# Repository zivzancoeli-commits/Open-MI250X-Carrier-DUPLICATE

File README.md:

> **DUPLICATE working copy — not the original.**
> Original: https://github.com/zivzancoeli-commits/Open-MI250X-Carrier
> Marked duplicate: 2026-08-21

# Open MI250X Carrier

## Purpose
This project collects public evidence needed to design a minimal open-source carrier board for surplus AMD Instinct MI250X OAM modules. It is organized as a reverse-engineering knowledge base: public documentation is collected first, facts are extracted into notes, and unknown or proprietary behavior is tracked instead of assumed.

## Workflow
- Collect public links and local reference copies in [02_AMD_Docs](02_AMD_Docs/) and [13_Reference_Docs](13_Reference_Docs/).
- Extract design-relevant facts into [09_AI_Notes](09_AI_Notes/), separating verified information from questions.
- Use research in [08_Research_Papers](08_Research_Papers/) to understand topology, bandwidth, and system context before design decisions.
- Carry verified mechanical, PCIe, power, cooling, firmware, and software assumptions into schematic, layout, prototype, and validation work.

## Top-Level Folders
- [02_AMD_Docs](02_AMD_Docs/): upstream public links for OAM, AMD matrix cores, ROCm compatibility, and MI250X software support.
- [08_Research_Papers](08_Research_Papers/): architecture and data-movement research, currently focused on topology and bandwidth.
- [09_AI_Notes](09_AI_Notes/): topic notes for architecture, PCIe, power, cooling, clocking, management, ideas, questions, and unknowns.
- [13_Reference_Docs](13_Reference_Docs/): local indexes and reference material for AMD, ROCm, OAM/OCP, Molex, cooling, firmware, memory, and components.

## Known Information
- Manual project status items: gather public documentation, understand OAM, identify undocumented interfaces, create architecture, draw schematic, PCB layout, prototype.
- Manual note: undocumented behavior should be tracked as an open question rather than assumed.
- `Wanted_Documents.rtf` tracks OAM, AMD, PCIe, power, cooling, and photo references; no image files are currently present.
- MP2975 is listed as believed present on MI250X, but not visually confirmed.

## Project Roadmap
1. Documentation Collection
2. Knowledge Extraction
3. Reverse Engineering
4. Schematic Design
5. PCB Layout
6. Prototype
7. Bring-up and Validation

## Open Questions
- Mechanical, baseboard, connector, PCIe routing, REFCLK, PMBus, VRM, and OAM thermal references are listed as missing or incomplete.
- Three local PDFs could not be read because they report invalid PDF structure.

## TODO
- Keep `Wanted_Documents.rtf` aligned with files added under `13_Reference_Docs`.
- Move verified findings into `09_AI_Notes` with clear evidence and uncertainty labels.

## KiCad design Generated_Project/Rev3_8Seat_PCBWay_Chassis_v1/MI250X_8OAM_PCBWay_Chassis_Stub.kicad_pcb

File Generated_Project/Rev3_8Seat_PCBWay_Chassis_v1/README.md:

# Rev3 — 8-seat chassis, 2-module first article (POWER+MECH)

**DO NOT ENERGIZE P48V** until Molex 1.2 A/contact at 48–59.5 V (2 oz) is written (ticket 167157).  
**Do not upload from this agent.** Eli uploads `fab/Rev3_8Seat_PCBWay_12L_492x372_qty5_gerbers.zip` if he accepts it.

Chamber B **OAM chassis PCB** only. Not a motherboard. Do not swap X11DPH-T.

- **First-article target: seats 0–1.** Without overlay, 2× MI250X = two modules **sit** and at most **GCD0** on each can be targeted (**2 GCDs**). **Not** 2× full-width (**4 GCDs**).
- Legal host PE today: Conn0 OCP `PCIE_*` = `PE_S0_GCD0_x16` + `PE_S1_GCD0_x16` toward the host keepout. GCD1 named-only. Not S1–S7. Conn1 has **0** `PCIE_*`.
- Host X11DPH-T: two GCD0 x16 **fit**; two full-width modules **do not**. **No CEM/MCIO MPN invented.**
- Same PCB populate **2 → 4 → 8**. Later-seat x16 names + SW0–SW3 DNP kept. Do not stuff switches this article.
- Pin names: OCP generic **v1.0**. **v1.x only.** r2.0 is UNUSABLE. P3V3 = Conn0 C1/C2.
- **P48V:** Anderson **6325G1** + 2× **1382** → star spines (not a 100 A flood) → per-seat **0476015.MR** 15 A. First populate F0/F1. Off-board 48 V: 240 V / 50 A single-phase class — **not** RST-5000-48 (3-phase).
- **P12V1 / P3V3:** **THL 40-4812WI** (40 W from 48 V) + **OKI-78SR-3.3/1.5-W36-C** (4.95 W from P12V1). No GPU VRM.
- TEST*/RFU/DO_NOT_USE **unmapped**. PVREF **not driven**. S1–S7 **no net**.
- Silk keeps **DO NOT ENERGIZE P48V**. PE stays unrouted (DNP switches).

| File | What |
|---|---|
| `fab/Rev3_8Seat_PCBWay_12L_492x372_qty5_gerbers.zip` | Gerbers, drill, IPC-356, PnP, FAB_NOTES, BOM |
| `docs/STATUS.md` | What Eli can upload vs what stays DNP |
| `docs/EPYC_2P_PUBLIC_SKETCH.md` | Public-facts 2P EPYC host sketch. **DO NOT FAB.** No SP5 pins, xGMI routes, SVI3 phases, or Gerbers. Buy H13/H14, MZ73, TURIN2D/GENOA2D, or AS-4124GQ-TNMI. Dual SP5 has 4× MI250X lanes; overlay still missing. |
| `docs/CONCEPT_8x_FULL_WIDTH.md` | Pointer to 8× full-width **CONCEPT** (ideas only) |
| `docs/LATE_BIND.md` | Pointer: reserved vs later-spin (**respin**, not silk ECO) |
| [`../Rev3_8Seat_FULLWIDTH_CONCEPT/LATE_BIND.md`](../Rev3_8Seat_FULLWIDTH_CONCEPT/LATE_BIND.md) | Late-bind table. **DO NOT FABRICATE** live PE. |
| [`../Rev3_8Seat_FULLWIDTH_CONCEPT/CONCEPT.md`](../Rev3_8Seat_FULLWIDTH_CONCEPT/CONCEPT.md) | 8× full-width fabric sketch. **DO NOT FABRICATE.** X11DPH-T cannot light 256 DS. |
| `docs/FAB_NOTES.md` | Stackup, skip-pin NC, do-not-energize |
| `docs/PCBWAY.md` | Guest quotes 2026-08-21. Agent does not upload. |
| `BOM.md` | PCB bill with buyable MPNs |
| `docs/previews/` | Top SVG/PNG |

```
python3 Generated_Project/Rev3_8Seat_PCBWay_Chassis_v1/tools/generate_from_v10_pinmap.py
python3 Generated_Project/Rev3_8Seat_PCBWay_Chassis_v1/tools/export_fab.py
```

Do not “Update PCB from Schematic”. Do not stuff PM8536 on this article. Do not upload to PCBWay from this tree. First article still cannot run 2 live GPUs without maps. **This zip will not work as a live GPU chassis if sent to PCBWay.**

**8× full-width CONCEPT** (sibling folder): ideas only. **DO NOT FABRICATE** as live PE. **DO NOT ENERGIZE.** Host stays X11DPH-T and **cannot light 8× full-width**. Routing 16× x16 + four 1311-ball escapes is a **respin** (`LATE_BIND.md`).

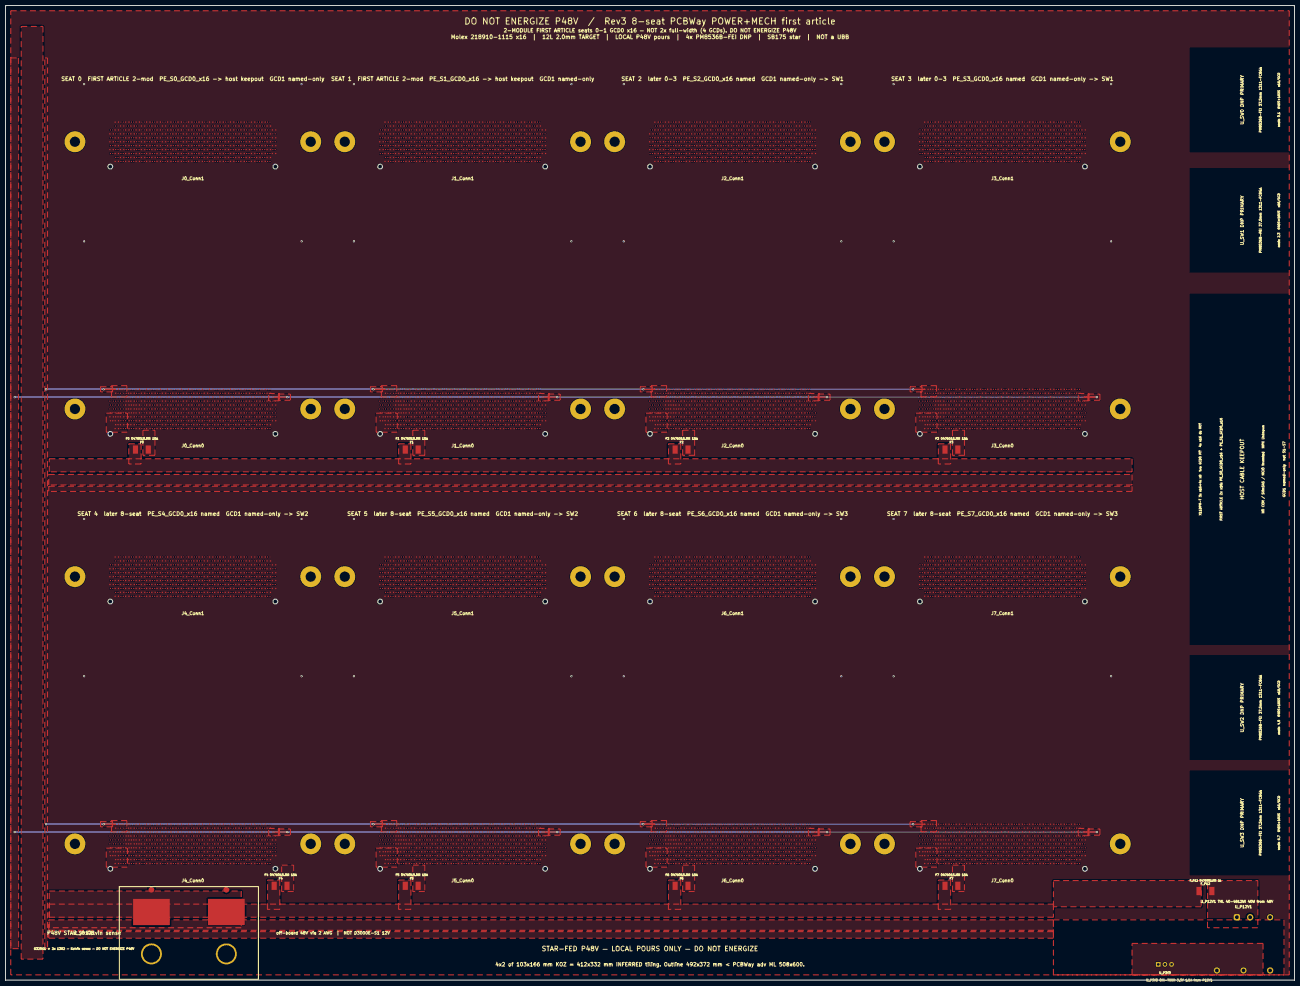
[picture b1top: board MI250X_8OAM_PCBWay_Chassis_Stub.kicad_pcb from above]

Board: 12 copper layers, 492.0 x 372.0 mm, 60 parts (0 on the bottom side), 22 nets.

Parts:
F0, F1, F2, F3, F4, F5, F6, F7: 0476015.MR; Fuse_Littelfuse-NANO2-451_453
F_P12: 0476002.MR; Fuse_Littelfuse-NANO2-451_453
H01, H02, H03, H04, H11, H12, H13, H14, H21, H22, H23, H24, H31, H32, H33, H34, H41, H42, H43, H44, H51, H52, H53, H54, H61, H62, H63, H64, H71, H72, H73, H74: NPTH_3.9; NPTH_3.9_Fig2
J0_Conn0, J0_Conn1, J1_Conn0, J1_Conn1, J2_Conn0, J2_Conn1, J3_Conn0, J3_Conn1, J4_Conn0, J4_Conn1, J5_Conn0, J5_Conn1, J6_Conn0, J6_Conn1, J7_Conn0, J7_Conn1: 218910-1115; 218910-1115_candidate
J_SB175: 6325G1_SB175; Anderson_SB175_2pole
U_P3V3: OKI-78SR-3.3/1.5-W36-C; Converter_DCDC_Murata_OKI-78SR_Vertical
U_P12V1: THL 40-4812WI; Converter_DCDC_TRACO_THL40-xxxxWI_THT

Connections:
GND: J0_Conn0.A5, J0_Conn0.A6, J0_Conn0.A9, J0_Conn0.A10, J0_Conn0.A13, J0_Conn0.A14, J0_Conn0.A17, J0_Conn0.A18, J0_Conn0.A21, J0_Conn0.A22, J0_Conn0.A25, J0_Conn0.A26, J0_Conn0.A29, J0_Conn0.A30, J0_Conn0.A33, J0_Conn0.A34, J0_Conn0.A37, J0_Conn0.A38, J0_Conn0.A41, J0_Conn0.A42, J0_Conn0.A45, J0_Conn0.A46, J0_Conn0.A49, J0_Conn0.A50, J0_Conn0.A53, J0_Conn0.A54, J0_Conn0.A57, J0_Conn0.A58, J0_Conn0.B3, J0_Conn0.B4, J0_Conn0.B7, J0_Conn0.B8, J0_Conn0.B11, J0_Conn0.B12, J0_Conn0.B15, J0_Conn0.B16, J0_Conn0.B19, J0_Conn0.B20, J0_Conn0.B23, J0_Conn0.B24, J0_Conn0.B27, J0_Conn0.B28, J0_Conn0.B31, J0_Conn0.B32, J0_Conn0.B35, J0_Conn0.B36, J0_Conn0.B39, J0_Conn0.B40, J0_Conn0.B43, J0_Conn0.B44, J0_Conn0.B47, J0_Conn0.B48, J0_Conn0.B51, J0_Conn0.B52, J0_Conn0.B55, J0_Conn0.B56, J0_Conn0.B57, J0_Conn0.B58, J0_Conn0.C5, J0_Conn0.C6, J0_Conn0.C9, J0_Conn0.C10, J0_Conn0.C13, J0_Conn0.C14, J0_Conn0.C17, J0_Conn0.C18, J0_Conn0.C21, J0_Conn0.C22, J0_Conn0.C25, J0_Conn0.C26, J0_Conn0.C29, J0_Conn0.C30, J0_Conn0.C33, J0_Conn0.C34, J0_Conn0.C37, J0_Conn0.C38, J0_Conn0.C41, J0_Conn0.C42, J0_Conn0.C45, J0_Conn0.C46, J0_Conn0.C49, J0_Conn0.C50, J0_Conn0.C53, J0_Conn0.C54, J0_Conn0.C57, J0_Conn0.C58, J0_Conn0.D3, J0_Conn0.D4, J0_Conn0.D7, J0_Conn0.D8, J0_Conn0.D11, J0_Conn0.D12, J0_Conn0.D15, J0_Conn0.D16, J0_Conn0.D19, J0_Conn0.D20, J0_Conn0.D23, J0_Conn0.D24, J0_Conn0.D27, J0_Conn0.D28, J0_Conn0.D31, J0_Conn0.D32, J0_Conn0.D35, J0_Conn0.D36, J0_Conn0.D39, J0_Conn0.D40, J0_Conn0.D43, J0_Conn0.D44, J0_Conn0.D47, J0_Conn0.D48, J0_Conn0.D51, J0_Conn0.D52, J0_Conn0.D55, J0_Conn0.D56, J0_Conn0.D57, J0_Conn0.D58, J0_Conn0.E1, J0_Conn0.E2, J0_Conn0.E5, J0_Conn0.E6, J0_Conn0.E9, J0_Conn0.E10, J0_Conn0.E13, J0_Conn0.E14, J0_Conn0.E17, J0_Conn0.E18, J0_Conn0.E21, J0_Conn0.E22, J0_Conn0.E25, J0_Conn0.E26, J0_Conn0.E29, J0_Conn0.E30, J0_Conn0.E33, J0_Conn0.E34, J0_Conn0.E37, J0_Conn0.E38, J0_Conn0.E41, J0_Conn0.E42, J0_Conn0.E45, J0_Conn0.E46, J0_Conn0.E49, J0_Conn0.E50, J0_Conn0.E53, J0_Conn0.E54, J0_Conn0.E55, J0_Conn0.E56, J0_Conn0.E57, J0_Conn0.E58, J0_Conn0.F3, J0_Conn0.F4, J0_Conn0.F7, J0_Conn0.F8, J0_Conn0.F11, J0_Conn0.F12, J0_Conn0.F15, J0_Conn0.F16, J0_Conn0.F19, J0_Conn0.F20, J0_Conn0.F23, J0_Conn0.F24, J0_Conn0.F27, J0_Conn0.F28, J0_Conn0.F31, J0_Conn0.F32, J0_Conn0.F35, J0_Conn0.F36, J0_Conn0.F39, J0_Conn0.F40, J0_Conn0.F43, J0_Conn0.F44, J0_Conn0.F47, J0_Conn0.F48, J0_Conn0.F51, J0_Conn0.F52, J0_Conn0.F53, J0_Conn0.F54, J0_Conn0.F55, J0_Conn0.F56, J0_Conn0.F57, J0_Conn0.F58, J0_Conn0.G5, J0_Conn0.G6, J0_Conn0.G9, J0_Conn0.G10, J0_Conn0.G13, J0_Conn0.G14, J0_Conn0.G17, J0_Conn0.G18, J0_Conn0.G21, J0_Conn0.G22, J0_Conn0.G25, J0_Conn0.G26, J0_Conn0.G29, J0_Conn0.G30, J0_Conn0.G33, J0_Conn0.G34, J0_Conn0.G37, J0_Conn0.G38, J0_Conn0.G41, J0_Conn0.G42, J0_Conn0.G45, J0_Conn0.G46, J0_Conn0.G49, J0_Conn0.G50, J0_Conn0.G53, J0_Conn0.G54, J0_Conn0.G55, J0_Conn0.G56, J0_Conn0.G57, J0_Conn0.G58, J0_Conn0.G59, J0_Conn0.G60, J0_Conn0.G61, J0_Conn0.G62, J0_Conn0.G63, J0_Conn0.G64, J0_Conn0.H3, J0_Conn0.H4, J0_Conn0.H7, J0_Conn0.H8, J0_Conn0.H11, J0_Conn0.H12, J0_Conn0.H15, J0_Conn0.H16, J0_Conn0.H19, J0_Conn0.H20, J0_Conn0.H23, J0_Conn0.H24, J0_Conn0.H27, J0_Conn0.H28, J0_Conn0.H31, J0_Conn0.H32, J0_Conn0.H35, J0_Conn0.H36, J0_Conn0.H39, J0_Conn0.H40, J0_Conn0.H43, J0_Conn0.H44, J0_Conn0.H47, J0_Conn0.H48, J0_Conn0.H51, J0_Conn0.H52, J0_Conn0.H55, J0_Conn0.H56, J0_Conn0.H57, J0_Conn0.J1, J0_Conn0.J2, J0_Conn0.J5, J0_Conn0.J6, J0_Conn0.J9, J0_Conn0.J10, J0_Conn0.J13, J0_Conn0.J14, J0_Conn0.J17, J0_Conn0.J18, J0_Conn0.J21, J0_Conn0.J22, J0_Conn0.J25, J0_Conn0.J26, J0_Conn0.J29, J0_Conn0.J30, J0_Conn0.J33, J0_Conn0.J34, J0_Conn0.J37, J0_Conn0.J38, J0_Conn0.J41, J0_Conn0.J42, J0_Conn0.J45, J0_Conn0.J46, J0_Conn0.J49, J0_Conn0.J50, J0_Conn0.J53, J0_Conn0.J54, J0_Conn0.J57, J0_Conn0.J58, J0_Conn0.J59, J0_Conn0.K3, J0_Conn0.K4, J0_Conn0.K7, J0_Conn0.K8, J0_Conn0.K11, J0_Conn0.K12, J0_Conn0.K15, J0_Conn0.K16, J0_Conn0.K19, J0_Conn0.K20, J0_Conn0.K23, J0_Conn0.K24, J0_Conn0.K27, J0_Conn0.K28, J0_Conn0.K31, J0_Conn0.K32, J0_Conn0.K35, J0_Conn0.K36, J0_Conn0.K39, J0_Conn0.K40, J0_Conn0.K43, J0_Conn0.K44, J0_Conn0.K47, J0_Conn0.K48, J0_Conn0.K51, J0_Conn0.K52, J0_Conn0.K55, J0_Conn0.K56, J0_Conn0.K57, J0_Conn0.L5, J0_Conn0.L6, J0_Conn0.L9, J0_Conn0.L10, J0_Conn0.L13, J0_Conn0.L14, J0_Conn0.L17, J0_Conn0.L18, J0_Conn0.L21, J0_Conn0.L22, J0_Conn0.L25, J0_Conn0.L26, J0_Conn0.L29, J0_Conn0.L30, J0_Conn0.L33, J0_Conn0.L34, J0_Conn0.L37, J0_Conn0.L38, J0_Conn0.L41, J0_Conn0.L42, J0_Conn0.L45, J0_Conn0.L46, J0_Conn0.L49, J0_Conn0.L50, J0_Conn0.L53, J0_Conn0.L54, J0_Conn0.L57, J0_Conn0.L58, J0_Conn0.L59, J0_Conn1.A5, J0_Conn1.A6, J0_Conn1.A9, J0_Conn1.A10, J0_Conn1.A13, J0_Conn1.A14, J0_Conn1.A17, J0_Conn1.A18, J0_Conn1.A21, J0_Conn1.A22, J0_Conn1.A25, J0_Conn1.A26, J0_Conn1.A29, J0_Conn1.A30, J0_Conn1.A33, J0_Conn1.A34, J0_Conn1.A37, J0_Conn1.A38, J0_Conn1.A41, J0_Conn1.A42, J0_Conn1.A45, J0_Conn1.A46, J0_Conn1.A49, J0_Conn1.A50, J0_Conn1.A53, J0_Conn1.A54, J0_Conn1.A57, J0_Conn1.A58, J0_Conn1.A61, J0_Conn1.A62, J0_Conn1.B3, J0_Conn1.B4, J0_Conn1.B7, J0_Conn1.B8, J0_Conn1.B11, J0_Conn1.B12, J0_Conn1.B15, J0_Conn1.B16, J0_Conn1.B19, J0_Conn1.B20, J0_Conn1.B23, J0_Conn1.B24, J0_Conn1.B27, J0_Conn1.B28, J0_Conn1.B31, J0_Conn1.B32, J0_Conn1.B35, J0_Conn1.B36, J0_Conn1.B39, J0_Conn1.B40, J0_Conn1.B43, J0_Conn1.B44, J0_Conn1.B47, J0_Conn1.B48, J0_Conn1.B51, J0_Conn1.B52, J0_Conn1.B55, J0_Conn1.B56, J0_Conn1.B59, J0_Conn1.B60, J0_Conn1.C1, J0_Conn1.C2, J0_Conn1.C5, J0_Conn1.C6, J0_Conn1.C9, J0_Conn1.C10, J0_Conn1.C13, J0_Conn1.C14, J0_Conn1.C17, J0_Conn1.C18, J0_Conn1.C21, J0_Conn1.C22, J0_Conn1.C25, J0_Conn1.C26, J0_Conn1.C29, J0_Conn1.C30, J0_Conn1.C33, J0_Conn1.C34, J0_Conn1.C37, J0_Conn1.C38, J0_Conn1.C41, J0_Conn1.C42, J0_Conn1.C45, J0_Conn1.C46, J0_Conn1.C49, J0_Conn1.C50, J0_Conn1.C53, J0_Conn1.C54, J0_Conn1.C57, J0_Conn1.C58, J0_Conn1.C61, J0_Conn1.C62, J0_Conn1.D3, J0_Conn1.D4, J0_Conn1.D7, J0_Conn1.D8, J0_Conn1.D11, J0_Conn1.D12, J0_Conn1.D15, J0_Conn1.D16, J0_Conn1.D19, J0_Conn1.D20, J0_Conn1.D23, J0_Conn1.D24, J0_Conn1.D27, J0_Conn1.D28, J0_Conn1.D31, J0_Conn1.D32, J0_Conn1.D35, J0_Conn1.D36, J0_Conn1.D39, J0_Conn1.D40, J0_Conn1.D43, J0_Conn1.D44, J0_Conn1.D47, J0_Conn1.D48, J0_Conn1.D51, J0_Conn1.D52, J0_Conn1.D55, J0_Conn1.D56, J0_Conn1.D59, J0_Conn1.D60, J0_Conn1.D63, J0_Conn1.D64, J0_Conn1.E1, J0_Conn1.E2, J0_Conn1.E5, J0_Conn1.E6, J0_Conn1.E9, J0_Conn1.E10, J0_Conn1.E13, J0_Conn1.E14, J0_Conn1.E17, J0_Conn1.E18, J0_Conn1.E21, J0_Conn1.E22, J0_Conn1.E25, J0_Conn1.E26, J0_Conn1.E29, J0_Conn1.E30, J0_Conn1.E33, J0_Conn1.E34, J0_Conn1.E37, J0_Conn1.E38, J0_Conn1.E41, J0_Conn1.E42, J0_Conn1.E45, J0_Conn1.E46, J0_Conn1.E49, J0_Conn1.E50, J0_Conn1.E53, J0_Conn1.E54, J0_Conn1.E57, J0_Conn1.E58, J0_Conn1.E61, J0_Conn1.E62, J0_Conn1.F3, J0_Conn1.F4, J0_Conn1.F7, J0_Conn1.F8, J0_Conn1.F11, J0_Conn1.F12, J0_Conn1.F15, J0_Conn1.F16, J0_Conn1.F19, J0_Conn1.F20, J0_Conn1.F23, J0_Conn1.F24, J0_Conn1.F27, J0_Conn1.F28, J0_Conn1.F31, J0_Conn1.F32, J0_Conn1.F35, J0_Conn1.F36, J0_Conn1.F39, J0_Conn1.F40, J0_Conn1.F43, J0_Conn1.F44, J0_Conn1.F47, J0_Conn1.F48, J0_Conn1.F51, J0_Conn1.F52, J0_Conn1.F55, J0_Conn1.F56, J0_Conn1.F59, J0_Conn1.F60, J0_Conn1.F63, J0_Conn1.F64, J0_Conn1.G1, J0_Conn1.G2, J0_Conn1.G5, J0_Conn1.G6, J0_Conn1.G9, J0_Conn1.G10, J0_Conn1.G13, J0_Conn1.G14, J0_Conn1.G17, J0_Conn1.G18, J0_Conn1.G21, J0_Conn1.G22, J0_Conn1.G25, J0_Conn1.G26, J0_Conn1.G29, J0_Conn1.G30, J0_Conn1.G33, J0_Conn1.G34, J0_Conn1.G37, J0_Conn1.G38, J0_Conn1.G41, J0_Conn1.G42, J0_Conn1.G45, J0_Conn1.G46, J0_Conn1.G49, J0_Conn1.G50, J0_Conn1.G53, J0_Conn1.G54, J0_Conn1.G57, J0_Conn1.G58, J0_Conn1.G61, J0_Conn1.G62, J0_Conn1.H3, J0_Conn1.H4, J0_Conn1.H7, J0_Conn1.H8, J0_Conn1.H11, J0_Conn1.H12, J0_Conn1.H15, J0_Conn1.H16, J0_Conn1.H19, J0_Conn1.H20, J0_Conn1.H23, J0_Conn1.H24, J0_Conn1.H27, J0_Conn1.H28, J0_Conn1.H31, J0_Conn1.H32, J0_Conn1.H35, J0_Conn1.H36, J0_Conn1.H39, J0_Conn1.H40, J0_Conn1.H43, J0_Conn1.H44, J0_Conn1.H47, J0_Conn1.H48, J0_Conn1.H51, J0_Conn1.H52, J0_Conn1.H55, J0_Conn1.H56, J0_Conn1.H59, J0_Conn1.H60, J0_Conn1.H63, J0_Conn1.H64, J0_Conn1.J1, J0_Conn1.J2, J0_Conn1.J5, J0_Conn1.J6, J0_Conn1.J9, J0_Conn1.J10, J0_Conn1.J13, J0_Conn1.J14, J0_Conn1.J17, J0_Conn1.J18, J0_Conn1.J21, J0_Conn1.J22, J0_Conn1.J25, J0_Conn1.J26, J0_Conn1.J29, J0_Conn1.J30, J0_Conn1.J33, J0_Conn1.J34, J0_Conn1.J37, J0_Conn1.J38, J0_Conn1.J41, J0_Conn1.J42, J0_Conn1.J45, J0_Conn1.J46, J0_Conn1.J49, J0_Conn1.J50, J0_Conn1.J53, J0_Conn1.J54, J0_Conn1.J57, J0_Conn1.J58, J0_Conn1.J61, J0_Conn1.J62, J0_Conn1.K3, J0_Conn1.K4, J0_Conn1.K7, J0_Conn1.K8, J0_Conn1.K11, J0_Conn1.K12, J0_Conn1.K15, J0_Conn1.K16, J0_Conn1.K19, J0_Conn1.K20, J0_Conn1.K23, J0_Conn1.K24, J0_Conn1.K27, J0_Conn1.K28, J0_Conn1.K31, J0_Conn1.K32, J0_Conn1.K35, J0_Conn1.K36, J0_Conn1.K39, J0_Conn1.K40, J0_Conn1.K43, J0_Conn1.K44, J0_Conn1.K47, J0_Conn1.K48, J0_Conn1.K51, J0_Conn1.K52, J0_Conn1.K55, J0_Conn1.K56, J0_Conn1.K59, J0_Conn1.K60, J0_Conn1.L5, J0_Conn1.L6, J0_Conn1.L9, J0_Conn1.L10, J0_Conn1.L13, J0_Conn1.L14, J0_Conn1.L17, J0_Conn1.L18, J0_Conn1.L21, J0_Conn1.L22, J0_Conn1.L25, J0_Conn1.L26, J0_Conn1.L29, J0_Conn1.L30, J0_Conn1.L33, J0_Conn1.L34, J0_Conn1.L37, J0_Conn1.L38, J0_Conn1.L41, J0_Conn1.L42, J0_Conn1.L45, J0_Conn1.L46, J0_Conn1.L49, J0_Conn1.L50, J0_Conn1.L53, J0_Conn1.L54, J0_Conn1.L57, J0_Conn1.L58, J0_Conn1.L61, J0_Conn1.L62, J1_Conn0.A5, J1_Conn0.A6, J1_Conn0.A9, J1_Conn0.A10, J1_Conn0.A13, J1_Conn0.A14, J1_Conn0.A17, J1_Conn0.A18, J1_Conn0.A21, J1_Conn0.A22, J1_Conn0.A25, J1_Conn0.A26, J1_Conn0.A29, J1_Conn0.A30, J1_Conn0.A33, J1_Conn0.A34, J1_Conn0.A37, J1_Conn0.A38, J1_Conn0.A41, J1_Conn0.A42, J1_Conn0.A45, J1_Conn0.A46, J1_Conn0.A49, J1_Conn0.A50, J1_Conn0.A53, J1_Conn0.A54, J1_Conn0.A57, J1_Conn0.A58, J1_Conn0.B3, J1_Conn0.B4, J1_Conn0.B7, J1_Conn0.B8, J1_Conn0.B11, J1_Conn0.B12, J1_Conn0.B15, J1_Conn0.B16, J1_Conn0.B19, J1_Conn0.B20, J1_Conn0.B23, J1_Conn0.B24, J1_Conn0.B27, J1_Conn0.B28, J1_Conn0.B31, J1_Conn0.B32, J1_Conn0.B35, J1_Conn0.B36, J1_Conn0.B39, J1_Conn0.B40, J1_Conn0.B43, J1_Conn0.B44, J1_Conn0.B47, J1_Conn0.B48, J1_Conn0.B51, J1_Conn0.B52, J1_Conn0.B55, J1_Conn0.B56, J1_Conn0.B57, J1_Conn0.B58, J1_Conn0.C5, J1_Conn0.C6, J1_Conn0.C9, J1_Conn0.C10, J1_Conn0.C13, J1_Conn0.C14, J1_Conn0.C17, J1_Conn0.C18, J1_Conn0.C21, J1_Conn0.C22, J1_Conn0.C25, J1_Conn0.C26, J1_Conn0.C29, J1_Conn0.C30, J1_Conn0.C33, J1_Conn0.C34, J1_Conn0.C37, J1_Conn0.C38, J1_Conn0.C41, J1_Conn0.C42, J1_Conn0.C45, J1_Conn0.C46, J1_Conn0.C49, J1_Conn0.C50, J1_Conn0.C53, J1_Conn0.C54, J1_Conn0.C57, J1_Conn0.C58, J1_Conn0.D3, J1_Conn0.D4, J1_Conn0.D7, J1_Conn0.D8, J1_Conn0.D11, J1_Conn0.D12, J1_Conn0.D15, J1_Conn0.D16, J1_Conn0.D19, J1_Conn0.D20, J1_Conn0.D23, J1_Conn0.D24, J1_Conn0.D27, J1_Conn0.D28, J1_Conn0.D31, J1_Conn0.D32, J1_Conn0.D35, J1_Conn0.D36, J1_Conn0.D39, J1_Conn0.D40, J1_Conn0.D43, J1_Conn0.D44, J1_Conn0.D47, J1_Conn0.D48, J1_Conn0.D51, J1_Conn0.D52, J1_Conn0.D55, J1_Conn0.D56, J1_Conn0.D57, J1_Conn0.D58, J1_Conn0.E1, J1_Conn0.E2, J1_Conn0.E5, J1_Conn0.E6, J1_Conn0.E9, J1_Conn0.E10, J1_Conn0.E13, J1_Conn0.E14, J1_Conn0.E17, J1_Conn0.E18, J1_Conn0.E21, J1_Conn0.E22, J1_Conn0.E25, J1_Conn0.E26, J1_Conn0.E29, J1_Conn0.E30, J1_Conn0.E33, J1_Conn0.E34, J1_Conn0.E37, J1_Conn0.E38, J1_Conn0.E41, J1_Conn0.E42, J1_Conn0.E45, J1_Conn0.E46, J1_Conn0.E49, J1_Conn0.E50, J1_Conn0.E53, J1_Conn0.E54, J1_Conn0.E55, J1_Conn0.E56, J1_Conn0.E57, J1_Conn0.E58, J1_Conn0.F3, J1_Conn0.F4, J1_Conn0.F7, J1_Conn0.F8, J1_Conn0.F11, J1_Conn0.F12, J1_Conn0.F15, J1_Conn0.F16, J1_Conn0.F19, J1_Conn0.F20, J1_Conn0.F23, J1_Conn0.F24, J1_Conn0.F27, J1_Conn0.F28, J1_Conn0.F31, J1_Conn0.F32, J1_Conn0.F35, J1_Conn0.F36, J1_Conn0.F39, J1_Conn0.F40, J1_Conn0.F43, J1_Conn0.F44, J1_Conn0.F47, J1_Conn0.F48, J1_Conn0.F51, J1_Conn0.F52, J1_Conn0.F53, J1_Conn0.F54, J1_Conn0.F55, J1_Conn0.F56, J1_Conn0.F57, J1_Conn0.F58, J1_Conn0.G5, J1_Conn0.G6, J1_Conn0.G9, J1_Conn0.G10, J1_Conn0.G13, J1_Conn0.G14, J1_Conn0.G17, J1_Conn0.G18, J1_Conn0.G21, J1_Conn0.G22, J1_Conn0.G25, J1_Conn0.G26, J1_Conn0.G29, J1_Conn0.G30, J1_Conn0.G33, J1_Conn0.G34, J1_Conn0.G37, J1_Conn0.G38, J1_Conn0.G41, J1_Conn0.G42, J1_Conn0.G45, J1_Conn0.G46, J1_Conn0.G49, J1_Conn0.G50, J1_Conn0.G53, J1_Conn0.G54, J1_Conn0.G55, J1_Conn0.G56, J1_Conn0.G57, J1_Conn0.G58, J1_Conn0.G59, J1_Conn0.G60, J1_Conn0.G61, J1_Conn0.G62, J1_Conn0.G63, J1_Conn0.G64, J1_Conn0.H3, J1_Conn0.H4, J1_Conn0.H7, J1_Conn0.H8, J1_Conn0.H11, J1_Conn0.H12, J1_Conn0.H15, J1_Conn0.H16, J1_Conn0.H19, J1_Conn0.H20, J1_Conn0.H23, J1_Conn0.H24, J1_Conn0.H27, J1_Conn0.H28, J1_Conn0.H31, J1_Conn0.H32, J1_Conn0.H35, J1_Conn0.H36, J1_Conn0.H39, J1_Conn0.H40, J1_Conn0.H43, J1_Conn0.H44, J1_Conn0.H47, J1_Conn0.H48, J1_Conn0.H51, J1_Conn0.H52, J1_Conn0.H55, J1_Conn0.H56, J1_Conn0.H57, J1_Conn0.J1, J1_Conn0.J2, J1_Conn0.J5, J1_Conn0.J6, J1_Conn0.J9, J1_Conn0.J10, J1_Conn0.J13, J1_Conn0.J14, J1_Conn0.J17, J1_Conn0.J18, J1_Conn0.J21, J1_Conn0.J22, J1_Conn0.J25, J1_Conn0.J26, J1_Conn0.J29, J1_Conn0.J30, J1_Conn0.J33, J1_Conn0.J34, J1_Conn0.J37, J1_Conn0.J38, J1_Conn0.J41, J1_Conn0.J42, J1_Conn0.J45, J1_Conn0.J46, J1_Conn0.J49, J1_Conn0.J50, J1_Conn0.J53, J1_Conn0.J54, J1_Conn0.J57, J1_Conn0.J58, J1_Conn0.J59, J1_Conn0.K3, J1_Conn0.K4, J1_Conn0.K7, J1_Conn0.K8, J1_Conn0.K11, J1_Conn0.K12, J1_Conn0.K15, J1_Conn0.K16, J1_Conn0.K19, J1_Conn0.K20, J1_Conn0.K23, J1_Conn0.K24, J1_Conn0.K27, J1_Conn0.K28, J1_Conn0.K31, J1_Conn0.K32, J1_Conn0.K35, J1_Conn0.K36, J1_Conn0.K39, J1_Conn0.K40, J1_Conn0.K43, J1_Conn0.K44, J1_Conn0.K47, J1_Conn0.K48, J1_Conn0.K51, J1_Conn0.K52, J1_Conn0.K55, J1_Conn0.K56, J1_Conn0.K57, J1_Conn0.L5, J1_Conn0.L6, J1_Conn0.L9, J1_Conn0.L10, J1_Conn0.L13, J1_Conn0.L14, J1_Conn0.L17, J1_Conn0.L18, J1_Conn0.L21, J1_Conn0.L22, J1_Conn0.L25, J1_Conn0.L26, J1_Conn0.L29, J1_Conn0.L30, J1_Conn0.L33, J1_Conn0.L34, J1_Conn0.L37, J1_Conn0.L38, J1_Conn0.L41, J1_Conn0.L42, J1_Conn0.L45, J1_Conn0.L46, J1_Conn0.L49, J1_Conn0.L50, J1_Conn0.L53, J1_Conn0.L54, J1_Conn0.L57, J1_Conn0.L58, J1_Conn0.L59, J1_Conn1.A5, J1_Conn1.A6, J1_Conn1.A9, J1_Conn1.A10, J1_Conn1.A13, J1_Conn1.A14, J1_Conn1.A17, J1_Conn1.A18, J1_Conn1.A21, J1_Conn1.A22, J1_Conn1.A25, J1_Conn1.A26, J1_Conn1.A29, J1_Conn1.A30, J1_Conn1.A33, J1_Conn1.A34, J1_Conn1.A37, J1_Conn1.A38, J1_Conn1.A41, J1_Conn1.A42, J1_Conn1.A45, J1_Conn1.A46, J1_Conn1.A49, J1_Conn1.A50, J1_Conn1.A53, J1_Conn1.A54, J1_Conn1.A57, J1_Conn1.A58, J1_Conn1.A61, J1_Conn1.A62, J1_Conn1.B3, J1_Conn1.B4, J1_Conn1.B7, J1_Conn1.B8, J1_Conn1.B11, J1_Conn1.B12, J1_Conn1.B15, J1_Conn1.B16, J1_Conn1.B19, J1_Conn1.B20, J1_Conn1.B23, J1_Conn1.B24, J1_Conn1.B27, J1_Conn1.B28, J1_Conn1.B31, J1_Conn1.B32, J1_Conn1.B35, J1_Conn1.B36, J1_Conn1.B39, J1_Conn1.B40, J1_Conn1.B43, J1_Conn1.B44, J1_Conn1.B47, J1_Conn1.B48, J1_Conn1.B51, J1_Conn1.B52, J1_Conn1.B55, J1_Conn1.B56, J1_Conn1.B59, J1_Conn1.B60, J1_Conn1.C1, J1_Conn1.C2, J1_Conn1.C5, J1_Conn1.C6, J1_Conn1.C9, J1_Conn1.C10, J1_Conn1.C13, J1_Conn1.C14, J1_Conn1.C17, J1_Conn1.C18, J1_Conn1.C21, J1_Conn1.C22, J1_Conn1.C25, J1_Conn1.C26, J1_Conn1.C29, J1_Conn1.C30, J1_Conn1.C33, J1_Conn1.C34, J1_Conn1.C37, J1_Conn1.C38, J1_Conn1.C41, J1_Conn1.C42, J1_Conn1.C45, J1_Conn1.C46, J1_Conn1.C49, J1_Conn1.C50, J1_Conn1.C53, J1_Conn1.C54, J1_Conn1.C57, J1_Conn1.C58, J1_Conn1.C61, J1_Conn1.C62, J1_Conn1.D3, J1_Conn1.D4, J1_Conn1.D7, J1_Conn1.D8, J1_Conn1.D11, J1_Conn1.D12, J1_Conn1.D15, J1_Conn1.D16, J1_Conn1.D19, J1_Conn1.D20, J1_Conn1.D23, J1_Conn1.D24, J1_Conn1.D27, J1_Conn1.D28, J1_Conn1.D31, J1_Conn1.D32, J1_Conn1.D35, J1_Conn1.D36, J1_Conn1.D39, J1_Conn1.D40, J1_Conn1.D43, J1_Conn1.D44, J1_Conn1.D47, J1_Conn1.D48, J1_Conn1.D51, J1_Conn1.D52, J1_Conn1.D55, J1_Conn1.D56, J1_Conn1.D59, J1_Conn1.D60, J1_Conn1.D63, J1_Conn1.D64, J1_Conn1.E1, J1_Conn1.E2, J1_Conn1.E5, J1_Conn1.E6, J1_Conn1.E9, J1_Conn1.E10, J1_Conn1.E13, J1_Conn1.E14, J1_Conn1.E17, J1_Conn1.E18, J1_Conn1.E21, J1_Conn1.E22, J1_Conn1.E25, J1_Conn1.E26, J1_Conn1.E29, J1_Conn1.E30, J1_Conn1.E33, J1_Conn1.E34, J1_Conn1.E37, J1_Conn1.E38, J1_Conn1.E41, J1_Conn1.E42, J1_Conn1.E45, J1_Conn1.E46, J1_Conn1.E49, J1_Conn1.E50, J1_Conn1.E53, J1_Conn1.E54, J1_Conn1.E57, J1_Conn1.E58, J1_Conn1.E61, J1_Conn1.E62, J1_Conn1.F3, J1_Conn1.F4, J1_Conn1.F7, J1_Conn1.F8, J1_Conn1.F11, J1_Conn1.F12, J1_Conn1.F15, J1_Conn1.F16, J1_Conn1.F19, J1_Conn1.F20, J1_Conn1.F23, J1_Conn1.F24, J1_Conn1.F27, J1_Conn1.F28, J1_Conn1.F31, J1_Conn1.F32, J1_Conn1.F35, J1_Conn1.F36, J1_Conn1.F39, J1_Conn1.F40, J1_Conn1.F43, J1_Conn1.F44, J1_Conn1.F47, J1_Conn1.F48, J1_Conn1.F51, J1_Conn1.F52, J1_Conn1.F55, J1_Conn1.F56, J1_Conn1.F59, J1_Conn1.F60, J1_Conn1.F63, J1_Conn1.F64, J1_Conn1.G1, J1_Conn1.G2, J1_Conn1.G5, J1_Conn1.G6, J1_Conn1.G9, J1_Conn1.G10, J1_Conn1.G13, J1_Conn1.G14, J1_Conn1.G17, J1_Conn1.G18, J1_Conn1.G21, J1_Conn1.G22, J1_Conn1.G25, J1_Conn1.G26, J1_Conn1.G29, J1_Conn1.G30, J1_Conn1.G33, J1_Conn1.G34, J1_Conn1.G37, J1_Conn1.G38, J1_Conn1.G41, J1_Conn1.G42, J1_Conn1.G45, J1_Conn1.G46, J1_Conn1.G49, J1_Conn1.G50, J1_Conn1.G53, J1_Conn1.G54, J1_Conn1.G57, J1_Conn1.G58, J1_Conn1.G61, J1_Conn1.G62, J1_Conn1.H3, J1_Conn1.H4, J1_Conn1.H7, J1_Conn1.H8, J1_Conn1.H11, J1_Conn1.H12, J1_Conn1.H15, J1_Conn1.H16, J1_Conn1.H19, J1_Conn1.H20, J1_Conn1.H23, J1_Conn1.H24, J1_Conn1.H27, J1_Conn1.H28, J1_Conn1.H31, J1_Conn1.H32, J1_Conn1.H35, J1_Conn1.H36, J1_Conn1.H39, J1_Conn1.H40, J1_Conn1.H43, J1_Conn1.H44, J1_Conn1.H47, J1_Conn1.H48, J1_Conn1.H51, J1_Conn1.H52, J1_Conn1.H55, J1_Conn1.H56, J1_Conn1.H59, J1_Conn1.H60, J1_Conn1.H63, J1_Conn1.H64, J1_Conn1.J1, J1_Conn1.J2, J1_Conn1.J5, J1_Conn1.J6, J1_Conn1.J9, J1_Conn1.J10, J1_Conn1.J13, J1_Conn1.J14, J1_Conn1.J17, J1_Conn1.J18, J1_Conn1.J21, J1_Conn1.J22, J1_Conn1.J25, J1_Conn1.J26, J1_Conn1.J29, J1_Conn1.J30, J1_Conn1.J33, J1_Conn1.J34, J1_Conn1.J37, J1_Conn1.J38, J1_Conn1.J41, J1_Conn1.J42, J1_Conn1.J45, J1_Conn1.J46, J1_Conn1.J49, J1_Conn1.J50, J1_Conn1.J53, J1_Conn1.J54, J1_Conn1.J57, J1_Conn1.J58, J1_Conn1.J61, J1_Conn1.J62, J1_Conn1.K3, J1_Conn1.K4, J1_Conn1.K7, J1_Conn1.K8, J1_Conn1.K11, J1_Conn1.K12, J1_Conn1.K15, J1_Conn1.K16, J1_Conn1.K19, J1_Conn1.K20, J1_Conn1.K23, J1_Conn1.K24, J1_Conn1.K27, J1_Conn1.K28, J1_Conn1.K31, J1_Conn1.K32, J1_Conn1.K35, J1_Conn1.K36, J1_Conn1.K39, J1_Conn1.K40, J1_Conn1.K43, J1_Conn1.K44, J1_Conn1.K47, J1_Conn1.K48, J1_Conn1.K51, J1_Conn1.K52, J1_Conn1.K55, J1_Conn1.K56, J1_Conn1.K59, J1_Conn1.K60, J1_Conn1.L5, J1_Conn1.L6, J1_Conn1.L9, J1_Conn1.L10, J1_Conn1.L13, J1_Conn1.L14, J1_Conn1.L17, J1_Conn1.L18, J1_Conn1.L21, J1_Conn1.L22, J1_Conn1.L25, J1_Conn1.L26, J1_Conn1.L29, J1_Conn1.L30, J1_Conn1.L33, J1_Conn1.L34, J1_Conn1.L37, J1_Conn1.L38, J1_Conn1.L41, J1_Conn1.L42, J1_Conn1.L45, J1_Conn1.L46, J1_Conn1.L49, J1_Conn1.L50, J1_Conn1.L53, J1_Conn1.L54, J1_Conn1.L57, J1_Conn1.L58, J1_Conn1.L61, J1_Conn1.L62, J2_Conn0.A5, J2_Conn0.A6, J2_Conn0.A9, J2_Conn0.A10, J2_Conn0.A13, J2_Conn0.A14, J2_Conn0.A17, J2_Conn0.A18, J2_Conn0.A21, J2_Conn0.A22, J2_Conn0.A25, J2_Conn0.A26, J2_Conn0.A29, J2_Conn0.A30, J2_Conn0.A33, J2_Conn0.A34, J2_Conn0.A37, J2_Conn0.A38, J2_Conn0.A41, J2_Conn0.A42, J2_Conn0.A45, J2_Conn0.A46, J2_Conn0.A49, J2_Conn0.A50, J2_Conn0.A53, J2_Conn0.A54, J2_Conn0.A57, J2_Conn0.A58, J2_Conn0.B3, J2_Conn0.B4, J2_Conn0.B7, J2_Conn0.B8, J2_Conn0.B11, J2_Conn0.B12, J2_Conn0.B15, J2_Conn0.B16, J2_Conn0.B19, J2_Conn0.B20, J2_Conn0.B23, J2_Conn0.B24, J2_Conn0.B27, J2_Conn0.B28, J2_Conn0.B31, J2_Conn0.B32, J2_Conn0.B35, J2_Conn0.B36, J2_Conn0.B39, J2_Conn0.B40, J2_Conn0.B43, J2_Conn0.B44, J2_Conn0.B47, J2_Conn0.B48, J2_Conn0.B51, J2_Conn0.B52, J2_Conn0.B55, J2_Conn0.B56, J2_Conn0.B57, J2_Conn0.B58, J2_Conn0.C5, J2_Conn0.C6, J2_Conn0.C9, J2_Conn0.C10, J2_Conn0.C13, J2_Conn0.C14, J2_Conn0.C17, J2_Conn0.C18, J2_Conn0.C21, J2_Conn0.C22, J2_Conn0.C25, J2_Conn0.C26, J2_Conn0.C29, J2_Conn0.C30, J2_Conn0.C33, J2_Conn0.C34, J2_Conn0.C37, J2_Conn0.C38, J2_Conn0.C41, J2_Conn0.C42, J2_Conn0.C45, J2_Conn0.C46, J2_Conn0.C49, J2_Conn0.C50, J2_Conn0.C53, J2_Conn0.C54, J2_Conn0.C57, J2_Conn0.C58, J2_Conn0.D3, J2_Conn0.D4, J2_Conn0.D7, J2_Conn0.D8, J2_Conn0.D11, J2_Conn0.D12, J2_Conn0.D15, J2_Conn0.D16, J2_Conn0.D19, J2_Conn0.D20, J2_Conn0.D23, J2_Conn0.D24, J2_Conn0.D27, J2_Conn0.D28, J2_Conn0.D31, J2_Conn0.D32, J2_Conn0.D35, J2_Conn0.D36, J2_Conn0.D39, J2_Conn0.D40, J2_Conn0.D43, J2_Conn0.D44, J2_Conn0.D47, J2_Conn0.D48, J2_Conn0.D51, J2_Conn0.D52, J2_Conn0.D55, J2_Conn0.D56, J2_Conn0.D57, J2_Conn0.D58, J2_Conn0.E1, J2_Conn0.E2, J2_Conn0.E5, J2_Conn0.E6, J2_Conn0.E9, J2_Conn0.E10, J2_Conn0.E13, J2_Conn0.E14, J2_Conn0.E17, J2_Conn0.E18, J2_Conn0.E21, J2_Conn0.E22, J2_Conn0.E25, J2_Conn0.E26, J2_Conn0.E29, J2_Conn0.E30, J2_Conn0.E33, J2_Conn0.E34, J2_Conn0.E37, J2_Conn0.E38, J2_Conn0.E41, J2_Conn0.E42, J2_Conn0.E45, J2_Conn0.E46, J2_Conn0.E49, J2_Conn0.E50, J2_Conn0.E53, J2_Conn0.E54, J2_Conn0.E55, J2_Conn0.E56, J2_Conn0.E57, J2_Conn0.E58, J2_Conn0.F3, J2_Conn0.F4, J2_Conn0.F7, J2_Conn0.F8, J2_Conn0.F11, J2_Conn0.F12, J2_Conn0.F15, J2_Conn0.F16, J2_Conn0.F19, J2_Conn0.F20, J2_Conn0.F23, J2_Conn0.F24, J2_Conn0.F27, J2_Conn0.F28, J2_Conn0.F31, J2_Conn0.F32, J2_Conn0.F35, J2_Conn0.F36, J2_Conn0.F39, J2_Conn0.F40, J2_Conn0.F43, J2_Conn0.F44, J2_Conn0.F47, J2_Conn0.F48, J2_Conn0.F51, J2_Conn0.F52, J2_Conn0.F53, J2_Conn0.F54, J2_Conn0.F55, J2_Conn0.F56, J2_Conn0.F57, J2_Conn0.F58, J2_Conn0.G5, J2_Conn0.G6, J2_Conn0.G9, J2_Conn0.G10, J2_Conn0.G13, J2_Conn0.G14, J2_Conn0.G17, J2_Conn0.G18, J2_Conn0.G21, J2_Conn0.G22, J2_Conn0.G25, J2_Conn0.G26, J2_Conn0.G29, J2_Conn0.G30, J2_Conn0.G33, J2_Conn0.G34, J2_Conn0.G37, J2_Conn0.G38, J2_Conn0.G41, J2_Conn0.G42, J2_Conn0.G45, J2_Conn0.G46, J2_Conn0.G49, J2_Conn0.G50, J2_Conn0.G53, J2_Conn0.G54, J2_Conn0.G55, J2_Conn0.G56, J2_Conn0.G57, J2_Conn0.G58, J2_Conn0.G59, J2_Conn0.G60, J2_Conn0.G61, J2_Conn0.G62, J2_Conn0.G63, J2_Conn0.G64, J2_Conn0.H3, J2_Conn0.H4, J2_Conn0.H7, J2_Conn0.H8, J2_Conn0.H11, J2_Conn0.H12, J2_Conn0.H15, J2_Conn0.H16, J2_Conn0.H19, J2_Conn0.H20, J2_Conn0.H23, J2_Conn0.H24, J2_Conn0.H27, J2_Conn0.H28, J2_Conn0.H31, J2_Conn0.H32, J2_Conn0.H35, J2_Conn0.H36, J2_Conn0.H39, J2_Conn0.H40, J2_Conn0.H43, J2_Conn0.H44, J2_Conn0.H47, J2_Conn0.H48, J2_Conn0.H51, J2_Conn0.H52, J2_Conn0.H55, J2_Conn0.H56, J2_Conn0.H57, J2_Conn0.J1, J2_Conn0.J2, J2_Conn0.J5, J2_Conn0.J6, J2_Conn0.J9, J2_Conn0.J10, J2_Conn0.J13, J2_Conn0.J14, J2_Conn0.J17, J2_Conn0.J18, J2_Conn0.J21, J2_Conn0.J22, J2_Conn0.J25, J2_Conn0.J26, J2_Conn0.J29, J2_Conn0.J30, J2_Conn0.J33, J2_Conn0.J34, J2_Conn0.J37, J2_Conn0.J38, J2_Conn0.J41, J2_Conn0.J42, J2_Conn0.J45, J2_Conn0.J46, J2_Conn0.J49, J2_Conn0.J50, J2_Conn0.J53, J2_Conn0.J54, J2_Conn0.J57, J2_Conn0.J58, J2_Conn0.J59, J2_Conn0.K3, J2_Conn0.K4, J2_Conn0.K7, J2_Conn0.K8, J2_Conn0.K11, J2_Conn0.K12, J2_Conn0.K15, J2_Conn0.K16, J2_Conn0.K19, J2_Conn0.K20, J2_Conn0.K23, J2_Conn0.K24, J2_Conn0.K27, J2_Conn0.K28, J2_Conn0.K31, J2_Conn0.K32, J2_Conn0.K35, J2_Conn0.K36, J2_Conn0.K39, J2_Conn0.K40, J2_Conn0.K43, J2_Conn0.K44, J2_Conn0.K47, J2_Conn0.K48, J2_Conn0.K51, J2_Conn0.K52, J2_Conn0.K55, J2_Conn0.K56, J2_Conn0.K57, J2_Conn0.L5, J2_Conn0.L6, J2_Conn0.L9, J2_Conn0.L10, J2_Conn0.L13, J2_Conn0.L14, J2_Conn0.L17, J2_Conn0.L18, J2_Conn0.L21, J2_Conn0.L22, J2_Conn0.L25, J2_Conn0.L26, J2_Conn0.L29, J2_Conn0.L30, J2_Conn0.L33, J2_Conn0.L34, J2_Conn0.L37, J2_Conn0.L38, J2_Conn0.L41, J2_Conn0.L42, J2_Conn0.L45, J2_Conn0.L46, J2_Conn0.L49, J2_Conn0.L50, J2_Conn0.L53, J2_Conn0.L54, J2_Conn0.L57, J2_Conn0.L58, J2_Conn0.L59, J2_Conn1.A5, J2_Conn1.A6, J2_Conn1.A9, J2_Conn1.A10, J2_Conn1.A13, J2_Conn1.A14, J2_Conn1.A17, J2_Conn1.A18, J2_Conn1.A21, J2_Conn1.A22, J2_Conn1.A25, J2_Conn1.A26, J2_Conn1.A29, J2_Conn1.A30, J2_Conn1.A33, J2_Conn1.A34, J2_Conn1.A37, J2_Conn1.A38, J2_Conn1.A41, J2_Conn1.A42, J2_Conn1.A45, J2_Conn1.A46, J2_Conn1.A49, J2_Conn1.A50, J2_Conn1.A53, J2_Conn1.A54, J2_Conn1.A57, J2_Conn1.A58, J2_Conn1.A61, J2_Conn1.A62, J2_Conn1.B3, J2_Conn1.B4, J2_Conn1.B7, J2_Conn1.B8, J2_Conn1.B11, J2_Conn1.B12, J2_Conn1.B15, J2_Conn1.B16, J2_Conn1.B19, J2_Conn1.B20, J2_Conn1.B23, J2_Conn1.B24, J2_Conn1.B27, J2_Conn1.B28, J2_Conn1.B31, J2_Conn1.B32, J2_Conn1.B35, J2_Conn1.B36, J2_Conn1.B39, J2_Conn1.B40, J2_Conn1.B43, J2_Conn1.B44, J2_Conn1.B47, J2_Conn1.B48, J2_Conn1.B51, J2_Conn1.B52, J2_Conn1.B55, J2_Conn1.B56, J2_Conn1.B59, J2_Conn1.B60, J2_Conn1.C1, J2_Conn1.C2, J2_Conn1.C5, J2_Conn1.C6, J2_Conn1.C9, J2_Conn1.C10, J2_Conn1.C13, J2_Conn1.C14, J2_Conn1.C17, J2_Conn1.C18, J2_Conn1.C21, J2_Conn1.C22, J2_Conn1.C25, J2_Conn1.C26, J2_Conn1.C29, J2_Conn1.C30, J2_Conn1.C33, J2_Conn1.C34, J2_Conn1.C37, J2_Conn1.C38, J2_Conn1.C41, J2_Conn1.C42, J2_Conn1.C45, J2_Conn1.C46, J2_Conn1.C49, J2_Conn1.C50, J2_Conn1.C53, J2_Conn1.C54, J2_Conn1.C57, J2_Conn1.C58, J2_Conn1.C61, J2_Conn1.C62, J2_Conn1.D3, J2_Conn1.D4, J2_Conn1.D7, J2_Conn1.D8, J2_Conn1.D11, J2_Conn1.D12, J2_Conn1.D15, J2_Conn1.D16, J2_Conn1.D19, J2_Conn1.D20, J2_Conn1.D23, J2_Conn1.D24, J2_Conn1.D27, J2_Conn1.D28, J2_Conn1.D31, J2_Conn1.D32, J2_Conn1.D35, J2_Conn1.D36, J2_Conn1.D39, J2_Conn1.D40, J2_Conn1.D43, J2_Conn1.D44, J2_Conn1.D47, J2_Conn1.D48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
OAM0_PVREF: J0_Conn0.G1, J0_Conn0.G2
OAM1_PVREF: J1_Conn0.G1, J1_Conn0.G2
OAM2_PVREF: J2_Conn0.G1, J2_Conn0.G2
OAM3_PVREF: J3_Conn0.G1, J3_Conn0.G2
OAM4_PVREF: J4_Conn0.G1, J4_Conn0.G2
OAM5_PVREF: J5_Conn0.G1, J5_Conn0.G2
OAM6_PVREF: J6_Conn0.G1, J6_Conn0.G2
OAM7_PVREF: J7_Conn0.G1, J7_Conn0.G2
P3V3: J0_Conn0.C1, J0_Conn0.C2, J1_Conn0.C1, J1_Conn0.C2, J2_Conn0.C1, J2_Conn0.C2, J3_Conn0.C1, J3_Conn0.C2, J4_Conn0.C1, J4_Conn0.C2, J5_Conn0.C1, J5_Conn0.C2, J6_Conn0.C1, J6_Conn0.C2, J7_Conn0.C1, J7_Conn0.C2, U_P3V3.3
P12V1: J0_Conn0.A59, J0_Conn0.A60, J0_Conn0.A61, J0_Conn0.A62, J0_Conn0.B62, J1_Conn0.A59, J1_Conn0.A60, J1_Conn0.A61, J1_Conn0.A62, J1_Conn0.B62, J2_Conn0.A59, J2_Conn0.A60, J2_Conn0.A61, J2_Conn0.A62, J2_Conn0.B62, J3_Conn0.A59, J3_Conn0.A60, J3_Conn0.A61, J3_Conn0.A62, J3_Conn0.B62, J4_Conn0.A59, J4_Conn0.A60, J4_Conn0.A61, J4_Conn0.A62, J4_Conn0.B62, J5_Conn0.A59, J5_Conn0.A60, J5_Conn0.A61, J5_Conn0.A62, J5_Conn0.B62, J6_Conn0.A59, J6_Conn0.A60, J6_Conn0.A61, J6_Conn0.A62, J6_Conn0.B62, J7_Conn0.A59, J7_Conn0.A60, J7_Conn0.A61, J7_Conn0.A62, J7_Conn0.B62, U_P3V3.1, U_P12V1.3
P12V2: J0_Conn0.B59, J0_Conn0.B60, J0_Conn0.B61, J0_Conn0.C59, J0_Conn0.C60, J0_Conn0.C61, J0_Conn0.C62, J0_Conn0.C63, J0_Conn0.C64, J0_Conn0.D59, J0_Conn0.D60, J0_Conn0.D61, J0_Conn0.D62, J0_Conn0.D63, J0_Conn0.D64, J0_Conn0.E59, J0_Conn0.E60, J0_Conn0.E61, J0_Conn0.E62, J0_Conn0.E63, J0_Conn0.E64, J0_Conn0.F59, J0_Conn0.F60, J0_Conn0.F61, J0_Conn0.F62, J0_Conn0.F63, J0_Conn0.F64, J1_Conn0.B59, J1_Conn0.B60, J1_Conn0.B61, J1_Conn0.C59, J1_Conn0.C60, J1_Conn0.C61, J1_Conn0.C62, J1_Conn0.C63, J1_Conn0.C64, J1_Conn0.D59, J1_Conn0.D60, J1_Conn0.D61, J1_Conn0.D62, J1_Conn0.D63, J1_Conn0.D64, J1_Conn0.E59, J1_Conn0.E60, J1_Conn0.E61, J1_Conn0.E62, J1_Conn0.E63, J1_Conn0.E64, J1_Conn0.F59, J1_Conn0.F60, J1_Conn0.F61, J1_Conn0.F62, J1_Conn0.F63, J1_Conn0.F64, J2_Conn0.B59, J2_Conn0.B60, J2_Conn0.B61, J2_Conn0.C59, J2_Conn0.C60, J2_Conn0.C61, J2_Conn0.C62, J2_Conn0.C63, J2_Conn0.C64, J2_Conn0.D59, J2_Conn0.D60, J2_Conn0.D61, J2_Conn0.D62, J2_Conn0.D63, J2_Conn0.D64, J2_Conn0.E59, J2_Conn0.E60, J2_Conn0.E61, J2_Conn0.E62, J2_Conn0.E63, J2_Conn0.E64, J2_Conn0.F59, J2_Conn0.F60, J2_Conn0.F61, J2_Conn0.F62, J2_Conn0.F63, J2_Conn0.F64, J3_Conn0.B59, J3_Conn0.B60, J3_Conn0.B61, J3_Conn0.C59, J3_Conn0.C60, J3_Conn0.C61, J3_Conn0.C62, J3_Conn0.C63, J3_Conn0.C64, J3_Conn0.D59, J3_Conn0.D60, J3_Conn0.D61, J3_Conn0.D62, J3_Conn0.D63, J3_Conn0.D64, J3_Conn0.E59, J3_Conn0.E60, J3_Conn0.E61, J3_Conn0.E62, J3_Conn0.E63, J3_Conn0.E64, J3_Conn0.F59, J3_Conn0.F60, J3_Conn0.F61, J3_Conn0.F62, J3_Conn0.F63, J3_Conn0.F64, J4_Conn0.B59, J4_Conn0.B60, J4_Conn0.B61, J4_Conn0.C59, J4_Conn0.C60, J4_Conn0.C61, J4_Conn0.C62, J4_Conn0.C63, J4_Conn0.C64, J4_Conn0.D59, J4_Conn0.D60, J4_Conn0.D61, J4_Conn0.D62, J4_Conn0.D63, J4_Conn0.D64, J4_Conn0.E59, J4_Conn0.E60, J4_Conn0.E61, J4_Conn0.E62, J4_Conn0.E63, J4_Conn0.E64, J4_Conn0.F59, J4_Conn0.F60, J4_Conn0.F61, J4_Conn0.F62, J4_Conn0.F63, J4_Conn0.F64, J5_Conn0.B59, J5_Conn0.B60, J5_Conn0.B61, J5_Conn0.C59, J5_Conn0.C60, J5_Conn0.C61, J5_Conn0.C62, J5_Conn0.C63, J5_Conn0.C64, J5_Conn0.D59, J5_Conn0.D60, J5_Conn0.D61, J5_Conn0.D62, J5_Conn0.D63, J5_Conn0.D64, J5_Conn0.E59, J5_Conn0.E60, J5_Conn0.E61, J5_Conn0.E62, J5_Conn0.E63, J5_Conn0.E64, J5_Conn0.F59, J5_Conn0.F60, J5_Conn0.F61, J5_Conn0.F62, J5_Conn0.F63, J5_Conn0.F64, J6_Conn0.B59, J6_Conn0.B60, J6_Conn0.B61, J6_Conn0.C59, J6_Conn0.C60, J6_Conn0.C61, J6_Conn0.C62, J6_Conn0.C63, J6_Conn0.C64, J6_Conn0.D59, J6_Conn0.D60, J6_Conn0.D61, J6_Conn0.D62, J6_Conn0.D63, J6_Conn0.D64, J6_Conn0.E59, J6_Conn0.E60, J6_Conn0.E61, J6_Conn0.E62, J6_Conn0.E63, J6_Conn0.E64, J6_Conn0.F59, J6_Conn0.F60, J6_Conn0.F61, J6_Conn0.F62, J6_Conn0.F63, J6_Conn0.F64, J7_Conn0.B59, J7_Conn0.B60, J7_Conn0.B61, J7_Conn0.C59, J7_Conn0.C60, J7_Conn0.C61, J7_Conn0.C62, J7_Conn0.C63, J7_Conn0.C64, J7_Conn0.D59, J7_Conn0.D60, J7_Conn0.D61, J7_Conn0.D62, J7_Conn0.D63, J7_Conn0.D64, J7_Conn0.E59, J7_Conn0.E60, J7_Conn0.E61, J7_Conn0.E62, J7_Conn0.E63, J7_Conn0.E64, J7_Conn0.F59, J7_Conn0.F60, J7_Conn0.F61, J7_Conn0.F62, J7_Conn0.F63, J7_Conn0.F64
P48V: F0.2, J0_Conn0.H59, J0_Conn0.H60, J0_Conn0.H61, J0_Conn0.H62, J0_Conn0.H63, J0_Conn0.H64, J0_Conn0.J61, J0_Conn0.J62, J0_Conn0.J63, J0_Conn0.J64, J0_Conn0.K59, J0_Conn0.K60, J0_Conn0.K61, J0_Conn0.K62, J0_Conn0.L61, J0_Conn0.L62
P48V_BRICK: F_P12.2, U_P12V1.1
P48V_S1: F1.2, J1_Conn0.H59, J1_Conn0.H60, J1_Conn0.H61, J1_Conn0.H62, J1_Conn0.H63, J1_Conn0.H64, J1_Conn0.J61, J1_Conn0.J62, J1_Conn0.J63, J1_Conn0.J64, J1_Conn0.K59, J1_Conn0.K60, J1_Conn0.K61, J1_Conn0.K62, J1_Conn0.L61, J1_Conn0.L62
P48V_S2: F2.2, J2_Conn0.H59, J2_Conn0.H60, J2_Conn0.H61, J2_Conn0.H62, J2_Conn0.H63, J2_Conn0.H64, J2_Conn0.J61, J2_Conn0.J62, J2_Conn0.J63, J2_Conn0.J64, J2_Conn0.K59, J2_Conn0.K60, J2_Conn0.K61, J2_Conn0.K62, J2_Conn0.L61, J2_Conn0.L62
P48V_S3: F3.2, J3_Conn0.H59, J3_Conn0.H60, J3_Conn0.H61, J3_Conn0.H62, J3_Conn0.H63, J3_Conn0.H64, J3_Conn0.J61, J3_Conn0.J62, J3_Conn0.J63, J3_Conn0.J64, J3_Conn0.K59, J3_Conn0.K60, J3_Conn0.K61, J3_Conn0.K62, J3_Conn0.L61, J3_Conn0.L62
P48V_S4: F4.2, J4_Conn0.H59, J4_Conn0.H60, J4_Conn0.H61, J4_Conn0.H62, J4_Conn0.H63, J4_Conn0.H64, J4_Conn0.J61, J4_Conn0.J62, J4_Conn0.J63, J4_Conn0.J64, J4_Conn0.K59, J4_Conn0.K60, J4_Conn0.K61, J4_Conn0.K62, J4_Conn0.L61, J4_Conn0.L62
P48V_S5: F5.2, J5_Conn0.H59, J5_Conn0.H60, J5_Conn0.H61, J5_Conn0.H62, J5_Conn0.H63, J5_Conn0.H64, J5_Conn0.J61, J5_Conn0.J62, J5_Conn0.J63, J5_Conn0.J64, J5_Conn0.K59, J5_Conn0.K60, J5_Conn0.K61, J5_Conn0.K62, J5_Conn0.L61, J5_Conn0.L62
P48V_S6: F6.2, J6_Conn0.H59, J6_Conn0.H60, J6_Conn0.H61, J6_Conn0.H62, J6_Conn0.H63, J6_Conn0.H64, J6_Conn0.J61, J6_Conn0.J62, J6_Conn0.J63, J6_Conn0.J64, J6_Conn0.K59, J6_Conn0.K60, J6_Conn0.K61, J6_Conn0.K62, J6_Conn0.L61, J6_Conn0.L62
P48V_S7: F7.2, J7_Conn0.H59, J7_Conn0.H60, J7_Conn0.H61, J7_Conn0.H62, J7_Conn0.H63, J7_Conn0.H64, J7_Conn0.J61, J7_Conn0.J62, J7_Conn0.J63, J7_Conn0.J64, J7_Conn0.K59, J7_Conn0.K60, J7_Conn0.K61, J7_Conn0.K62, J7_Conn0.L61, J7_Conn0.L62
P48V_STAR: F0.1, F1.1, F2.1, F3.1, F4.1, F5.1, F6.1, F7.1, F_P12.1, J_SB175.1, J_SB175.K+

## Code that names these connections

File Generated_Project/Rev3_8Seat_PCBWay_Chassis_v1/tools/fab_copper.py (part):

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
Routing policy:
  Do NOT flood P48V as one 100 A pour, and do NOT drag fat traces across the
  688-ball mezzanine. P48V_STAR lives in the left margin + two row spines in
  the copper-free channels south of each Conn0 row. Each seat fuse sits on
  that spine with pad 1 on STAR and pad 2 on a short per-seat P48V tongue
  into the Conn0 island. P12V1 / P3V3 use the same channels. F.Cu GND is
  low-priority and fills leftover (mezz GND pads + inner-plane stitches).

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                      rect(FP12_XY[0] + 0.8, FP12_XY[1] - 4, P12_MOD_XY[0] + 8, P12_MOD_XY[1] + 4),
                      priority=12, min_th=0.4))

    # P12V1 alley (x≈15.5) + row spines. Unique priorities where they touch.
    zones.append(zone(n_p12, "P12V1", "F.Cu", 0.25,
                      rect(15.0, 20, 16.05, 360), priority=30, min_th=0.35))
    zones.append(zone(n_p12, "P12V1", "F.Cu", 0.25,
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            alley_vias.add(key)
            vias.append(via((15.5, ay), n_p12, ("F.Cu", "B.Cu")))

    # P3V3: thin spines + local C1/C2 islands
    zones.append(zone(n_p3, "P3V3", "F.Cu", 0.20,
                      rect(2.0, 20, 5.0, 360), priority=50, min_th=0.3))
    zones.append(zone(n_p3, "P3V3", "F.Cu", 0.20,
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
